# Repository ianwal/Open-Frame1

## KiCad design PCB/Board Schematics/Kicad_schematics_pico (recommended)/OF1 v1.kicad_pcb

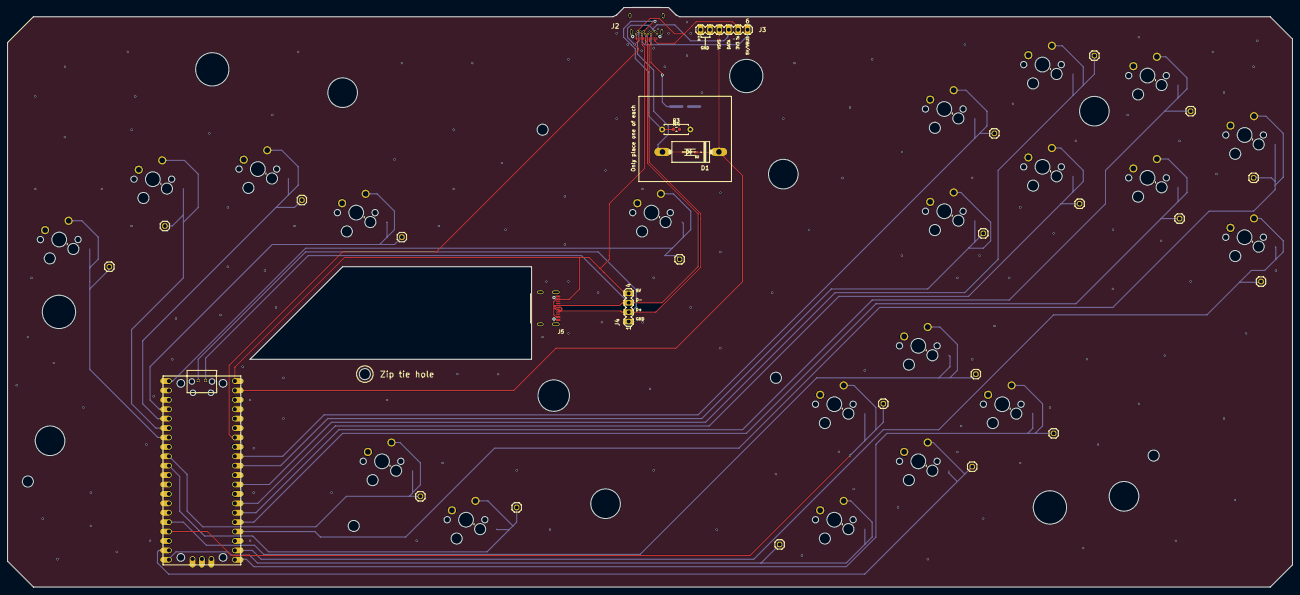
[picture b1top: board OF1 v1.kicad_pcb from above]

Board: 2 copper layers, 347.0 x 156.5 mm, 67 parts (1 on the bottom side), 29 nets.

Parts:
@HOLE0, @HOLE1, @HOLE2, @HOLE3, @HOLE4, @HOLE5, @HOLE6, @HOLE7, @HOLE8, @HOLE9, @HOLE10, @HOLE11, @HOLE12, @HOLE13, @HOLE14, @HOLE15, @HOLE16: (no value)
D1: 1N5400; DO201-15
D2: 1N5819HW-7-F; SOD3715X145N
J1: RPI_PICO-TH; RPI_PICO_TH
J2: MOLEX2171830001; 24P
J3: MA06-1
J4: MA04-1
J5: GT-USB-7010; 16P
JP2, JP3, JP4, JP5, JP6, JP7, JP8, JP9, JP10, JP11, JP12, JP13, JP14, JP15, JP16, JP17, JP18, JP19, JP20, JP21: PINHD-1X1; 1X01
R2, R4: 5.1k; R_0603_1608Metric
R3: 5.1k; R_Axial_DIN0207_L6.3mm_D2.5mm_P7.62mm_Horizontal
U$1, U$2, U$4, U$5, U$6, U$7, U$8, U$9, U$10, U$11, U$12, U$13, U$14, U$15, U$16, U$17, U$18, U$19, U$20, U$21: MX-B; MX-BOTH

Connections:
+5V: J1.VBUS, J2.A4 (A_VBUS), J2.A9 (A_VBUS), J2.B4 (B_VBUS), J2.B9 (B_VBUS), J3.6, J4.4, J5.A4/B9 (VBUS), J5.B4/A9 (VBUS)
/A: J1.GP14, JP20.1, U$20.P$2 (PIN1), U$20.P$3 (PIN1)
/B: J1.GP26_A0, JP10.1, U$13.P$2 (PIN1), U$13.P$3 (PIN1)
/C_DN: J1.GP15, JP21.1, U$21.P$2 (PIN1), U$21.P$3 (PIN1)
/C_LT: J1.GP13, JP18.1, U$18.P$2 (PIN1), U$18.P$3 (PIN1)
/C_RT: J1.GP16, JP19.1, U$19.P$2 (PIN1), U$19.P$3 (PIN1)
/C_UP: J1.GP12, JP17.1, U$17.P$2 (PIN1), U$17.P$3 (PIN1)
/D+: J1.TP3 (D-), J2.A6 (DA+), J2.B6 (DB+), J4.2, J5.A6 (D+), J5.B6 (D+)
/D-: J1.TP2 (D+), J2.A7 (DA-), J2.B7 (DB-), J4.3, J5.A7 (D-), J5.B7 (D-)
/DATA: J1.GP28_A2, J2.A11 (RX2+), J2.B11 (RX1+), J3.4
/DOWN: J1.GP3, JP4.1, U$4.P$2 (PIN1), U$4.P$3 (PIN1)
/L: J1.GP5, JP2.1, U$1.P$2 (PIN1), U$1.P$3 (PIN1)
/LEFT: J1.GP4, JP3.1, U$2.P$2 (PIN1), U$2.P$3 (PIN1)
/LS: J1.GP20, JP13.1, U$11.P$2 (PIN1), U$11.P$3 (PIN1)
/M1: J1.GP6, JP6.1, U$6.P$2 (PIN1), U$6.P$3 (PIN1)
/M2: J1.GP7, JP7.1, U$7.P$2 (PIN1), U$7.P$3 (PIN1)
/MS: J1.GP18, JP14.1, U$12.P$2 (PIN1), U$12.P$3 (PIN1)
/R: J1.GP27_A1, JP9.1, U$9.P$2 (PIN1), U$9.P$3 (PIN1)
/RIGHT: J1.GP2, JP5.1, U$5.P$2 (PIN1), U$5.P$3 (PIN1)
/START: J1.GP0, JP8.1, U$8.P$2 (PIN1), U$8.P$3 (PIN1)
/UP: J1.GP17, JP15.1, U$16.P$2 (PIN1), U$16.P$3 (PIN1)
/X: J1.GP21, JP11.1, U$14.P$2 (PIN1), U$14.P$3 (PIN1)
/Y: J1.GP22, JP12.1, U$10.P$2 (PIN1), U$10.P$3 (PIN1)
/Z: J1.GP19, JP16.1, U$15.P$2 (PIN1), U$15.P$3 (PIN1)
GND: J1.AGND, J1.GND@1 (GND), J1.GND@2 (GND), J1.GND@3 (GND), J1.GND@4 (GND), J1.GND@5 (GND), J1.GND@6 (GND), J1.GND@7 (GND), J1.GND@8 (GND), J2.A1 (GNDA), J2.A12 (GNDA), J2.B1 (GNDB), J2.B12 (GNDB), J2.SHIELD1 (SHIELD), J2.SHIELD2 (SHIELD), J2.SHIELD3 (SHIELD), J2.SHIELD4 (SHIELD), J3.1, J3.2, J4.1, J5.A1/B12 (GND), J5.B1/A12 (GND), J5.SHIELD1 (SHIELD), J5.SHIELD2 (SHIELD), J5.SHIELD3 (SHIELD), J5.SHIELD4 (SHIELD), R2.1, R3.2, R4.2, U$1.P$1 (PIN2), U$1.P$4 (PIN2), U$2.P$1 (PIN2), U$2.P$4 (PIN2), U$4.P$1 (PIN2), U$4.P$4 (PIN2), U$5.P$1 (PIN2), U$5.P$4 (PIN2), U$6.P$1 (PIN2), U$6.P$4 (PIN2), U$7.P$1 (PIN2), U$7.P$4 (PIN2), U$8.P$1 (PIN2), U$8.P$4 (PIN2), U$9.P$1 (PIN2), U$9.P$4 (PIN2), U$10.P$1 (PIN2), U$10.P$4 (PIN2), U$11.P$1 (PIN2), U$11.P$4 (PIN2), U$12.P$1 (PIN2), U$12.P$4 (PIN2), U$13.P$1 (PIN2), U$13.P$4 (PIN2), U$14.P$1 (PIN2), U$14.P$4 (PIN2), U$15.P$1 (PIN2), U$15.P$4 (PIN2), U$16.P$1 (PIN2), U$16.P$4 (PIN2), U$17.P$1 (PIN2), U$17.P$4 (PIN2), U$18.P$1 (PIN2), U$18.P$4 (PIN2), U$19.P$1 (PIN2), U$19.P$4 (PIN2), U$20.P$1 (PIN2), U$20.P$4 (PIN2), U$21.P$1 (PIN2), U$21.P$4 (PIN2)
unnamed: J2.A5 (CC1), R2.2
unnamed: J2.B5 (CC2), R3.1, R4.1
V+: D1.A, D2.A, J2.A2 (TX1+), J2.B2 (TX2+), J3.5
VCC: D1.C, D2.C (K), J1.VSYS, J3.3

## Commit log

2024-12-18 Move resistor to back
